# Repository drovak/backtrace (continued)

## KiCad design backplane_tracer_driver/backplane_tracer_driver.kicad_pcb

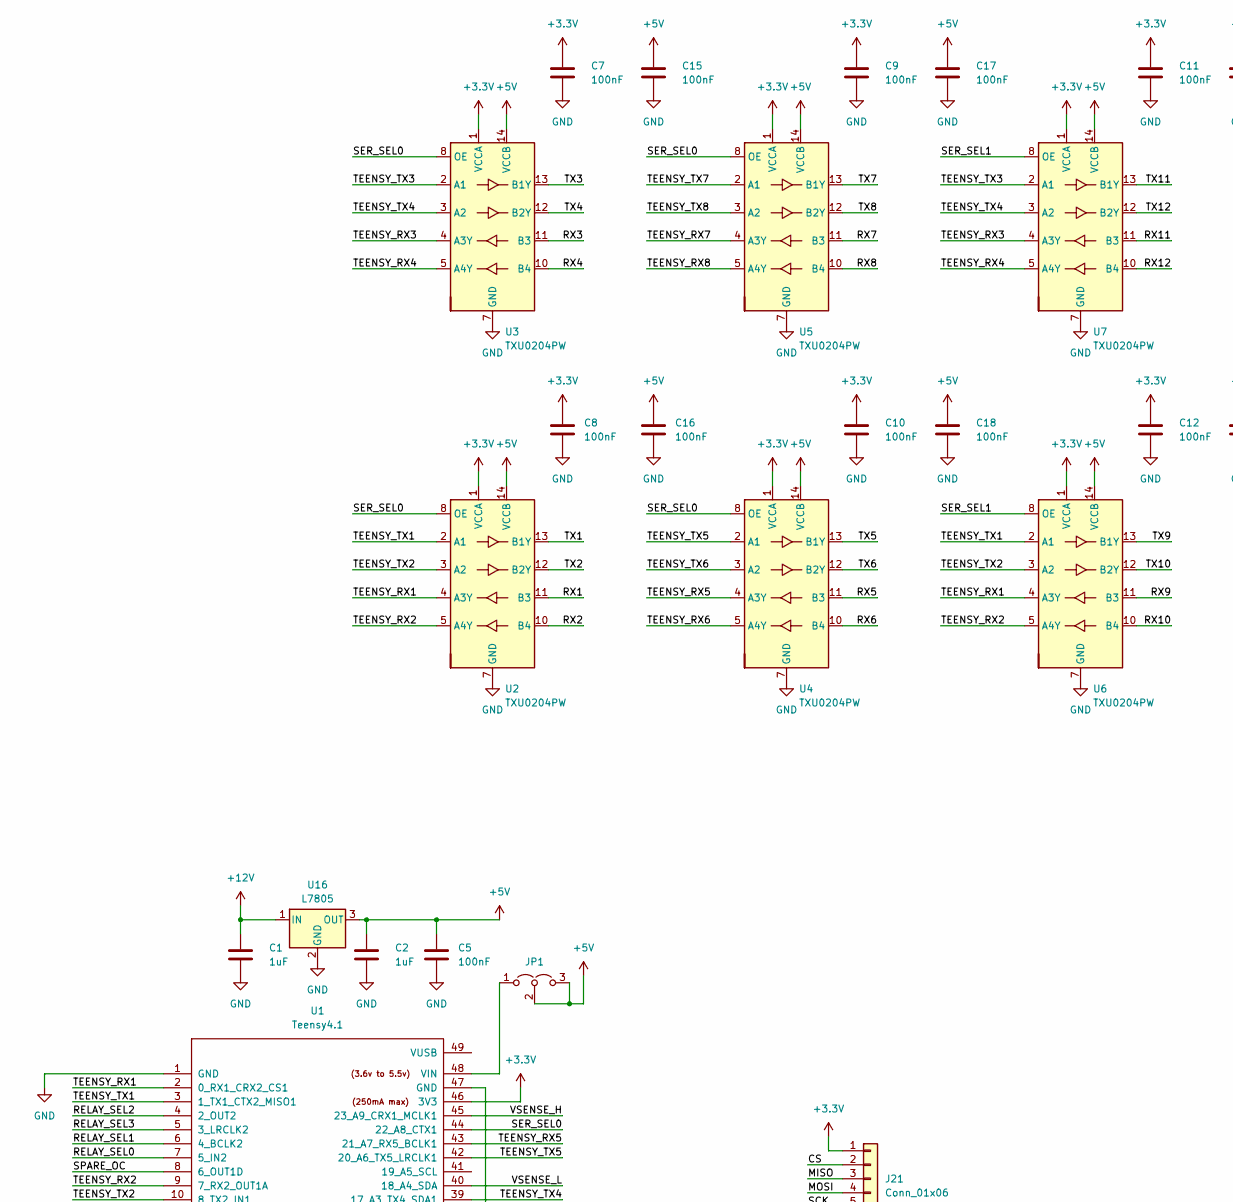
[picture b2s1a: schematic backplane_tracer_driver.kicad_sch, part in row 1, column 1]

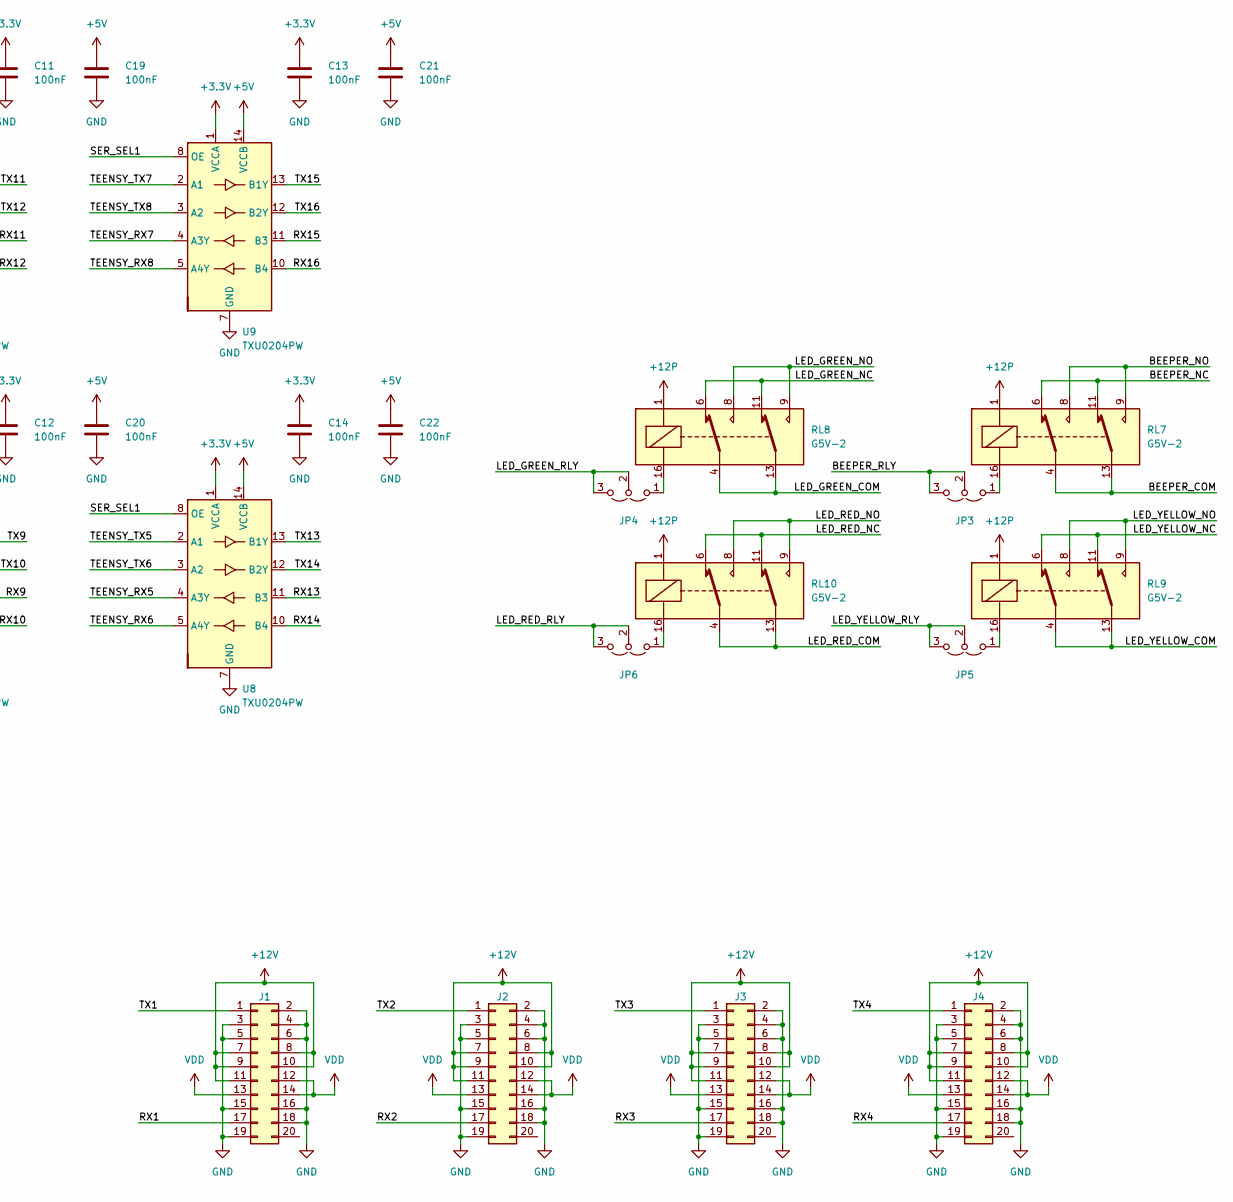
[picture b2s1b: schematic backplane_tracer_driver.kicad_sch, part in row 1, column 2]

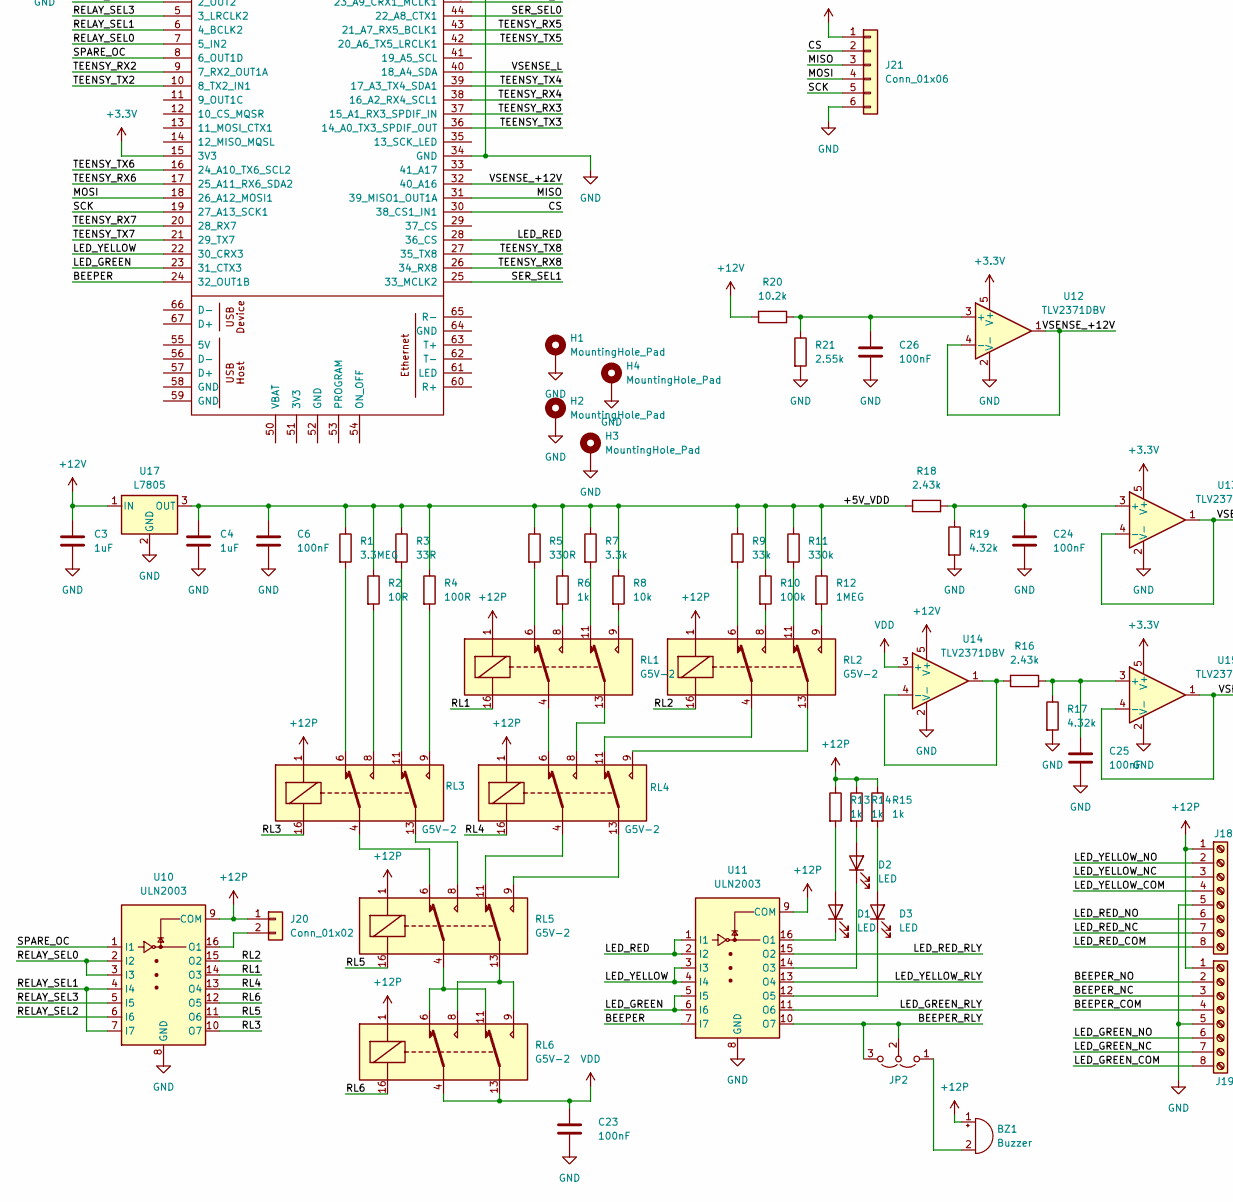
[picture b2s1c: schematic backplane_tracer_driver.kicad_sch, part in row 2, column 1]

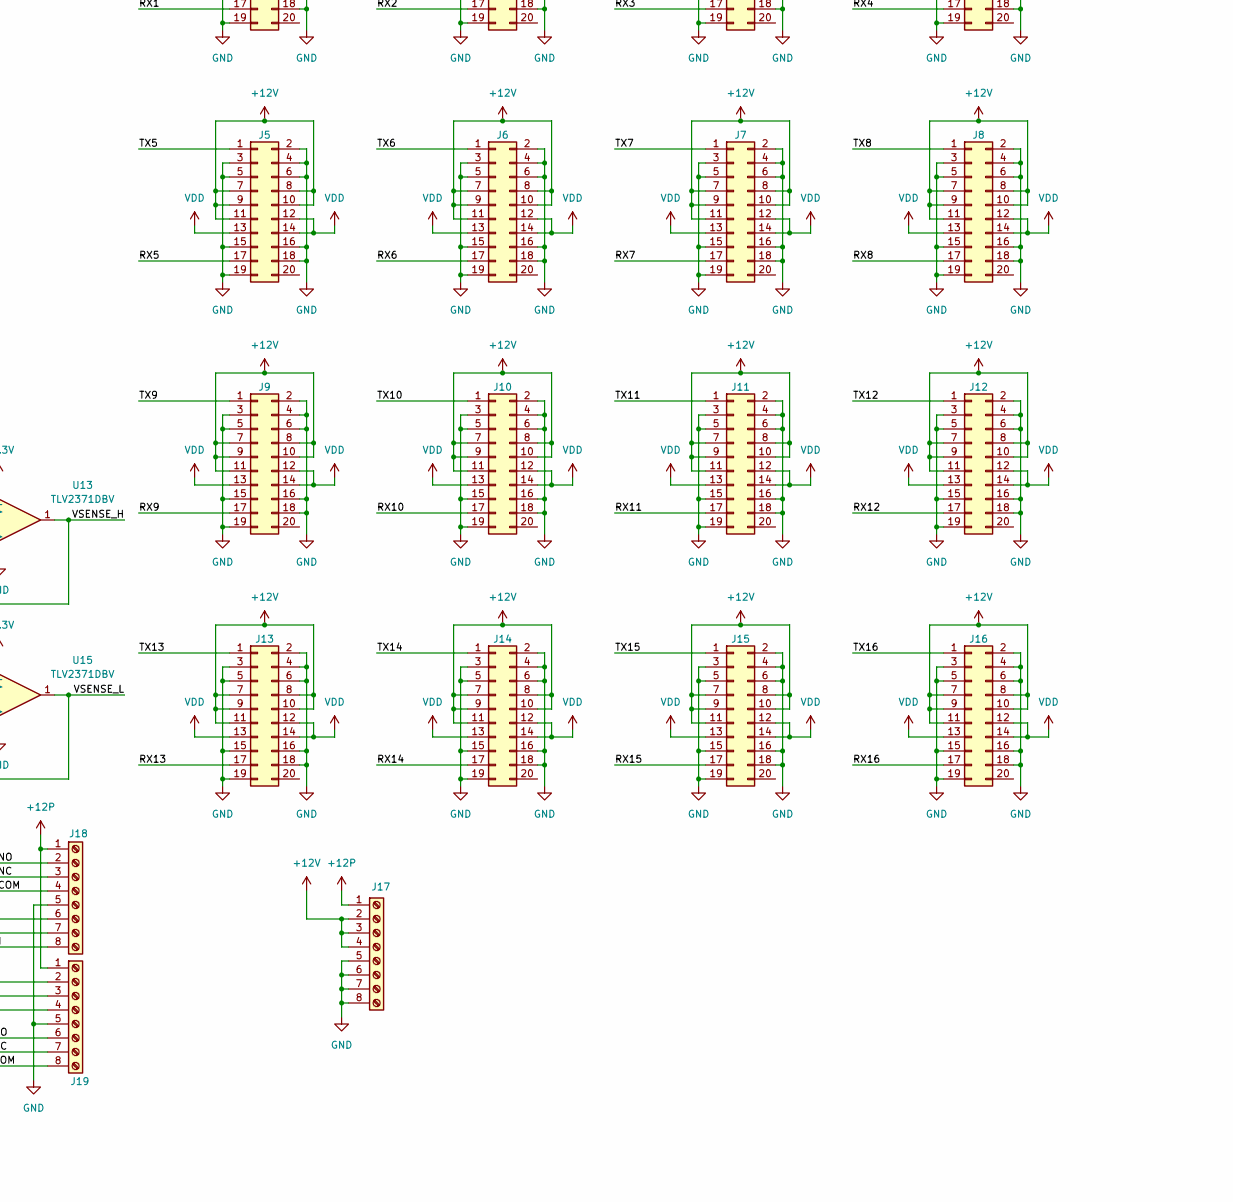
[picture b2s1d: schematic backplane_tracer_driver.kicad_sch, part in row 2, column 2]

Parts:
BZ1: Buzzer; Buzzer_12x9.5RM7.6
C1, C2, C3, C4: 1uF; C_0603_1608Metric_Pad1.08x0.95mm_HandSolder
C5, C6, C7, C8, C9, C10, C11, C12, C13, C14, C15, C16, C17, C18, C19, C20, C21, C22, C23, C24, C25, C26: 100nF; C_0603_1608Metric_Pad1.08x0.95mm_HandSolder
D1, D2, D3: LED; LED_D5.0mm
H1, H2, H3, H4: MountingHole_Pad; MountingHole_3.7mm_Pad_Via
J1, J2, J3, J4, J5, J6, J7, J8, J9, J10, J11, J12, J13, J14, J15, J16: 2x10 right angle IDC connector, 2.54mm pitch; IDC-Header_2x10_P2.54mm_Vertical_alt_silk; LCSC C5372876
J17, J18, J19: Screw_Terminal_01x08; PhoenixContact_PT_1,5_8-5,0-H_1935226
J20: Conn_01x02; PinHeader_1x02_P2.54mm_Vertical
J21: Conn_01x06; PinHeader_1x06_P2.54mm_Vertical
JP1, JP2, JP3, JP4, JP5, JP6: Jumper_3_Open; PinHeader_1x03_P2.54mm_Vertical
R1: 3.3MEG; R_Axial_DIN0207_L6.3mm_D2.5mm_P10.16mm_Horizontal
R2: 10R; R_Axial_Rideon_UB-5C_L0.5in_D0.25in_P0.8in_Horizontal
R3: 33R; R_Axial_DIN0614_L14.3mm_D5.7mm_P20.32mm_Horizontal
R4: 100R; R_Axial_DIN0207_L6.3mm_D2.5mm_P10.16mm_Horizontal
R5: 330R; R_Axial_DIN0204_L3.6mm_D1.6mm_P7.62mm_Horizontal
R6: 1k; R_Axial_DIN0204_L3.6mm_D1.6mm_P7.62mm_Horizontal
R7: 3.3k; R_Axial_DIN0204_L3.6mm_D1.6mm_P7.62mm_Horizontal
R8: 10k; R_Axial_DIN0204_L3.6mm_D1.6mm_P7.62mm_Horizontal
R9: 33k; R_Axial_DIN0204_L3.6mm_D1.6mm_P7.62mm_Horizontal
R10: 100k; R_Axial_DIN0204_L3.6mm_D1.6mm_P7.62mm_Horizontal
R11: 330k; R_Axial_DIN0204_L3.6mm_D1.6mm_P7.62mm_Horizontal
R12: 1MEG; R_Axial_DIN0204_L3.6mm_D1.6mm_P7.62mm_Horizontal
R13, R14, R15: 1k; R_0805_2012Metric
R16, R18: 2.43k; R_0805_2012Metric
R17, R19: 4.32k; R_0805_2012Metric
R20: 10.2k; R_0805_2012Metric
R21: 2.55k; R_0805_2012Metric
RL1, RL2, RL3, RL4, RL5, RL6, RL7, RL8, RL9, RL10: G5V-2; Relay_DPDT_Omron_G5V-2
U1: Teensy4.1; Teensy41
U2, U3, U4, U5, U6, U7, U8, U9: TXU0204PW; TSSOP-14_4.4x5mm_P0.65mm
U10, U11: ULN2003; SOIC-16_3.9x9.9mm_P1.27mm
U12, U13, U14, U15: TLV2371DBV; SOT-23-5
U16, U17: L7805; TO-220-3_Vertical

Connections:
+3.3V: C7.1, C8.1, C9.1, C10.1, C11.1, C12.1, C13.1, C14.1, J21.1, U1.15 (3V3), U1.46 (3V3), U2.1 (VCCA), U3.1 (VCCA), U4.1 (VCCA), U5.1 (VCCA), U6.1 (VCCA), U7.1 (VCCA), U8.1 (VCCA), U9.1 (VCCA), U12.5 (V+), U13.5 (V+), U15.5 (V+)
+5V: C2.1, C5.1, C15.1, C16.1, C17.1, C18.1, C19.1, C20.1, C21.1, C22.1, JP1.2 (C), JP1.3 (B), U2.14 (VCCB), U3.14 (VCCB), U4.14 (VCCB), U5.14 (VCCB), U6.14 (VCCB), U7.14 (VCCB), U8.14 (VCCB), U9.14 (VCCB), U16.3 (OUT)
+12P: BZ1.1 (+), J17.1, J18.1, J19.1, J20.1, R13.1, R14.1, R15.1, RL1.1, RL2.1, RL3.1, RL4.1, RL5.1, RL6.1, RL7.1, RL8.1, RL9.1, RL10.1, U10.9 (COM), U11.9 (COM)
+12V: C1.1, C3.1, J1.7, J1.8, J1.9, J1.10, J1.11, J2.7, J2.8, J2.9, J2.10, J2.11, J3.7, J3.8, J3.9, J3.10, J3.11, J4.7, J4.8, J4.9, J4.10, J4.11, J5.7, J5.8, J5.9, J5.10, J5.11, J6.7, J6.8, J6.9, J6.10, J6.11, J7.7, J7.8, J7.9, J7.10, J7.11, J8.7, J8.8, J8.9, J8.10, J8.11, J9.7, J9.8, J9.9, J9.10, J9.11, J10.7, J10.8, J10.9, J10.10, J10.11, J11.7, J11.8, J11.9, J11.10, J11.11, J12.7, J12.8, J12.9, J12.10, J12.11, J13.7, J13.8, J13.9, J13.10, J13.11, J14.7, J14.8, J14.9, J14.10, J14.11, J15.7, J15.8, J15.9, J15.10, J15.11, J16.7, J16.8, J16.9, J16.10, J16.11, J17.2, J17.3, J17.4, R20.1, U14.5 (V+), U16.1 (IN), U17.1 (IN)
/+5V_VDD: C4.1, C6.1, R1.1, R2.1, R3.1, R4.1, R5.1, R6.1, R7.1, R8.1, R9.1, R10.1, R11.1, R12.1, R18.1, U17.3 (OUT)
/BEEPER: U1.24 (32_OUT1B), U11.7 (I7)
/BEEPER_COM: J19.4, RL7.4, RL7.13
/BEEPER_NC: J19.3, RL7.6, RL7.11
/BEEPER_NO: J19.2, RL7.8, RL7.9
/BEEPER_RLY: JP2.2 (C), JP2.3 (B), JP3.2 (C), JP3.3 (B), U11.10 (O7)
/CS: J21.2, U1.30 (38_CS1_IN1)
/LED_GREEN: U1.23 (31_CTX3), U11.5 (I5), U11.6 (I6)
/LED_GREEN_COM: J19.8, RL8.4, RL8.13
/LED_GREEN_NC: J19.7, RL8.6, RL8.11
/LED_GREEN_NO: J19.6, RL8.8, RL8.9
/LED_GREEN_RLY: JP4.2 (C), JP4.3 (B), U11.11 (O6)
/LED_RED: U1.28 (36_CS), U11.1 (I1), U11.2 (I2)
/LED_RED_COM: J18.8, RL10.4, RL10.13
/LED_RED_NC: J18.7, RL10.6, RL10.11
/LED_RED_NO: J18.6, RL10.8, RL10.9
/LED_RED_RLY: JP6.2 (C), JP6.3 (B), U11.15 (O2)
/LED_YELLOW: U1.22 (30_CRX3), U11.3 (I3), U11.4 (I4)
/LED_YELLOW_COM: J18.4, RL9.4, RL9.13
/LED_YELLOW_NC: J18.3, RL9.6, RL9.11
/LED_YELLOW_NO: J18.2, RL9.8, RL9.9
/LED_YELLOW_RLY: JP5.2 (C), JP5.3 (B), U11.13 (O4)
/MISO: J21.3, U1.31 (39_MISO1_OUT1A)
/MOSI: J21.4, U1.18 (26_A12_MOSI1)
/RELAY_SEL0: U1.7 (5_IN2), U10.2 (I2), U10.3 (I3)
/RELAY_SEL1: U1.6 (4_BCLK2), U10.4 (I4), U10.7 (I7)
/RELAY_SEL2: U1.4 (2_OUT2), U10.6 (I6)
/RELAY_SEL3: U1.5 (3_LRCLK2), U10.5 (I5)
/RL1: RL1.16, U10.14 (O3)
/RL2: RL2.16, U10.15 (O2)
/RL3: RL3.16, U10.10 (O7)
/RL4: RL4.16, U10.13 (O4)
/RL5: RL5.16, U10.11 (O6)
/RL6: RL6.16, U10.12 (O5)
/RX1: J1.17, U2.11 (B3)
/RX2: J2.17, U2.10 (B4)
/RX3: J3.17, U3.11 (B3)
/RX4: J4.17, U3.10 (B4)
/RX5: J5.17, U4.11 (B3)
/RX6: J6.17, U4.10 (B4)
/RX7: J7.17, U5.11 (B3)
/RX8: J8.17, U5.10 (B4)
/RX9: J9.17, U6.11 (B3)
/RX10: J10.17, U6.10 (B4)
/RX11: J11.17, U7.11 (B3)
/RX12: J12.17, U7.10 (B4)
/RX13: J13.17, U8.11 (B3)
/RX14: J14.17, U8.10 (B4)
/RX15: J15.17, U9.11 (B3)
/RX16: J16.17, U9.10 (B4)
/SCK: J21.5, U1.19 (27_A13_SCK1)
/SER_SEL0: U1.44 (22_A8_CTX1), U2.8 (OE), U3.8 (OE), U4.8 (OE), U5.8 (OE)
/SER_SEL1: U1.25 (33_MCLK2), U6.8 (OE), U7.8 (OE), U8.8 (OE), U9.8 (OE)
/SPARE_OC: U1.8 (6_OUT1D), U10.1 (I1)
/TEENSY_RX1: U1.2 (0_RX1_CRX2_CS1), U2.4 (A3Y), U6.4 (A3Y)
/TEENSY_RX2: U1.9 (7_RX2_OUT1A), U2.5 (A4Y), U6.5 (A4Y)
/TEENSY_RX3: U1.37 (15_A1_RX3_SPDIF_IN), U3.4 (A3Y), U7.4 (A3Y)
/TEENSY_RX4: U1.38 (16_A2_RX4_SCL1), U3.5 (A4Y), U7.5 (A4Y)
/TEENSY_RX5: U1.43 (21_A7_RX5_BCLK1), U4.4 (A3Y), U8.4 (A3Y)
/TEENSY_RX6: U1.17 (25_A11_RX6_SDA2), U4.5 (A4Y), U8.5 (A4Y)
/TEENSY_RX7: U1.20 (28_RX7), U5.4 (A3Y), U9.4 (A3Y)
/TEENSY_RX8: U1.26 (34_RX8), U5.5 (A4Y), U9.5 (A4Y)
/TEENSY_TX1: U1.3 (1_TX1_CTX2_MISO1), U2.2 (A1), U6.2 (A1)
/TEENSY_TX2: U1.10 (8_TX2_IN1), U2.3 (A2), U6.3 (A2)
/TEENSY_TX3: U1.36 (14_A0_TX3_SPDIF_OUT), U3.2 (A1), U7.2 (A1)
/TEENSY_TX4: U1.39 (17_A3_TX4_SDA1), U3.3 (A2), U7.3 (A2)
/TEENSY_TX5: U1.42 (20_A6_TX5_LRCLK1), U4.2 (A1), U8.2 (A1)
/TEENSY_TX6: U1.16 (24_A10_TX6_SCL2), U4.3 (A2), U8.3 (A2)
/TEENSY_TX7: U1.21 (29_TX7), U5.2 (A1), U9.2 (A1)
/TEENSY_TX8: U1.27 (35_TX8), U5.3 (A2), U9.3 (A2)
/TX1: J1.1, U2.13 (B1Y)
/TX2: J2.1, U2.12 (B2Y)
/TX3: J3.1, U3.13 (B1Y)
/TX4: J4.1, U3.12 (B2Y)
/TX5: J5.1, U4.13 (B1Y)
/TX6: J6.1, U4.12 (B2Y)
/TX7: J7.1, U5.13 (B1Y)
/TX8: J8.1, U5.12 (B2Y)
/TX9: J9.1, U6.13 (B1Y)
/TX10: J10.1, U6.12 (B2Y)
/TX11: J11.1, U7.13 (B1Y)
/TX12: J12.1, U7.12 (B2Y)
/TX13: J13.1, U8.13 (B1Y)
/TX14: J14.1, U8.12 (B2Y)
/TX15: J15.1, U9.13 (B1Y)
/TX16: J16.1, U9.12 (B2Y)
/VSENSE_+12V: U1.32 (40_A16), U12.1, U12.4 (-)
/VSENSE_H: U1.45 (23_A9_CRX1_MCLK1), U13.1, U13.4 (-)
/VSENSE_L: U1.40 (18_A4_SDA), U15.1, U15.4 (-)
GND: C1.2, C2.2, C3.2, C4.2, C5.2, C6.2, C7.2, C8.2, C9.2, C10.2, C11.2, C12.2, C13.2, C14.2, C15.2, C16.2, C17.2, C18.2, C19.2, C20.2, C21.2, C22.2, C23.2, C24.2, C25.2, C26.2, H1.1, H2.1, H3.1, H4.1, J1.2, J1.3, J1.4, J1.5, J1.6, J1.15, J1.16, J1.18, J1.19, J2.2, J2.3, J2.4, J2.5, J2.6, J2.15, J2.16, J2.18, J2.19, J3.2, J3.3, J3.4, J3.5, J3.6, J3.15, J3.16, J3.18, J3.19, J4.2, J4.3, J4.4, J4.5, J4.6, J4.15, J4.16, J4.18, J4.19, J5.2, J5.3, J5.4, J5.5, J5.6, J5.15, J5.16, J5.18, J5.19, J6.2, J6.3, J6.4, J6.5, J6.6, J6.15, J6.16, J6.18, J6.19, J7.2, J7.3, J7.4, J7.5, J7.6, J7.15, J7.16, J7.18, J7.19, J8.2, J8.3, J8.4, J8.5, J8.6, J8.15, J8.16, J8.18, J8.19, J9.2, J9.3, J9.4, J9.5, J9.6, J9.15, J9.16, J9.18, J9.19, J10.2, J10.3, J10.4, J10.5, J10.6, J10.15, J10.16, J10.18, J10.19, J11.2, J11.3, J11.4, J11.5, J11.6, J11.15, J11.16, J11.18, J11.19, J12.2, J12.3, J12.4, J12.5, J12.6, J12.15, J12.16, J12.18, J12.19, J13.2, J13.3, J13.4, J13.5, J13.6, J13.15, J13.16, J13.18, J13.19, J14.2, J14.3, J14.4, J14.5, J14.6, J14.15, J14.16, J14.18, J14.19, J15.2, J15.3, J15.4, J15.5, J15.6, J15.15, J15.16, J15.18, J15.19, J16.2, J16.3, J16.4, J16.5, J16.6, J16.15, J16.16, J16.18, J16.19, J17.5, J17.6, J17.7, J17.8, J18.5, J19.5, J21.6, R17.2, R19.2, R21.2, U1.1 (GND), U1.34 (GND), U1.47 (GND), U2.7 (GND), U3.7 (GND), U4.7 (GND), U5.7 (GND), U6.7 (GND), U7.7 (GND), U8.7 (GND), U9.7 (GND), U10.8 (GND), U11.8 (GND), U12.2 (V-), U13.2 (V-), U14.2 (V-), U15.2 (V-), U16.2 (GND), U17.2 (GND)
unnamed: BZ1.2 (-), JP2.1 (A)
unnamed: D1.2 (A), R13.2
unnamed: D1.1 (K), U11.16 (O1)
unnamed: D2.2 (A), R14.2
unnamed: D2.1 (K), U11.14 (O3)
unnamed: D3.2 (A), R15.2
unnamed: D3.1 (K), U11.12 (O5)
unnamed: J20.2, U10.16 (O1)
unnamed: JP1.1 (A), U1.48 (VIN)
unnamed: JP3.1 (A), RL7.16
unnamed: JP4.1 (A), RL8.16
unnamed: JP5.1 (A), RL9.16
unnamed: JP6.1 (A), RL10.16
unnamed: R1.2, RL3.6
unnamed: R2.2, RL3.8
unnamed: R3.2, RL3.11
unnamed: R4.2, RL3.9
unnamed: R5.2, RL1.6
unnamed: R6.2, RL1.8
unnamed: R7.2, RL1.11
unnamed: R8.2, RL1.9
unnamed: R9.2, RL2.6
unnamed: R10.2, RL2.8
unnamed: R11.2, RL2.11
unnamed: R12.2, RL2.9
unnamed: RL1.4, RL4.6
unnamed: RL1.13, RL4.8
unnamed: RL2.4, RL4.11
unnamed: RL2.13, RL4.9
unnamed: RL3.4, RL5.6
unnamed: RL3.13, RL5.8
unnamed: RL4.4, RL5.11
unnamed: RL4.13, RL5.9
unnamed: RL5.4, RL6.6, RL6.11
unnamed: RL5.13, RL6.8, RL6.9
unnamed: C26.1, R20.2, R21.1, U12.3 (+)
unnamed: C24.1, R18.2, R19.1, U13.3 (+)
unnamed: R16.1, U14.1, U14.4 (-)
unnamed: C25.1, R16.2, R17.1, U15.3 (+)
VDD: C23.1, J1.12, J1.13, J1.14, J2.12, J2.13, J2.14, J3.12, J3.13, J3.14, J4.12, J4.13, J4.14, J5.12, J5.13, J5.14, J6.12, J6.13, J6.14, J7.12, J7.13, J7.14, J8.12, J8.13, J8.14, J9.12, J9.13, J9.14, J10.12, J10.13, J10.14, J11.12, J11.13, J11.14, J12.12, J12.13, J12.14, J13.12, J13.13, J13.14, J14.12, J14.13, J14.14, J15.12, J15.13, J15.14, J16.12, J16.13, J16.14, RL6.4, RL6.13, U14.3 (+)

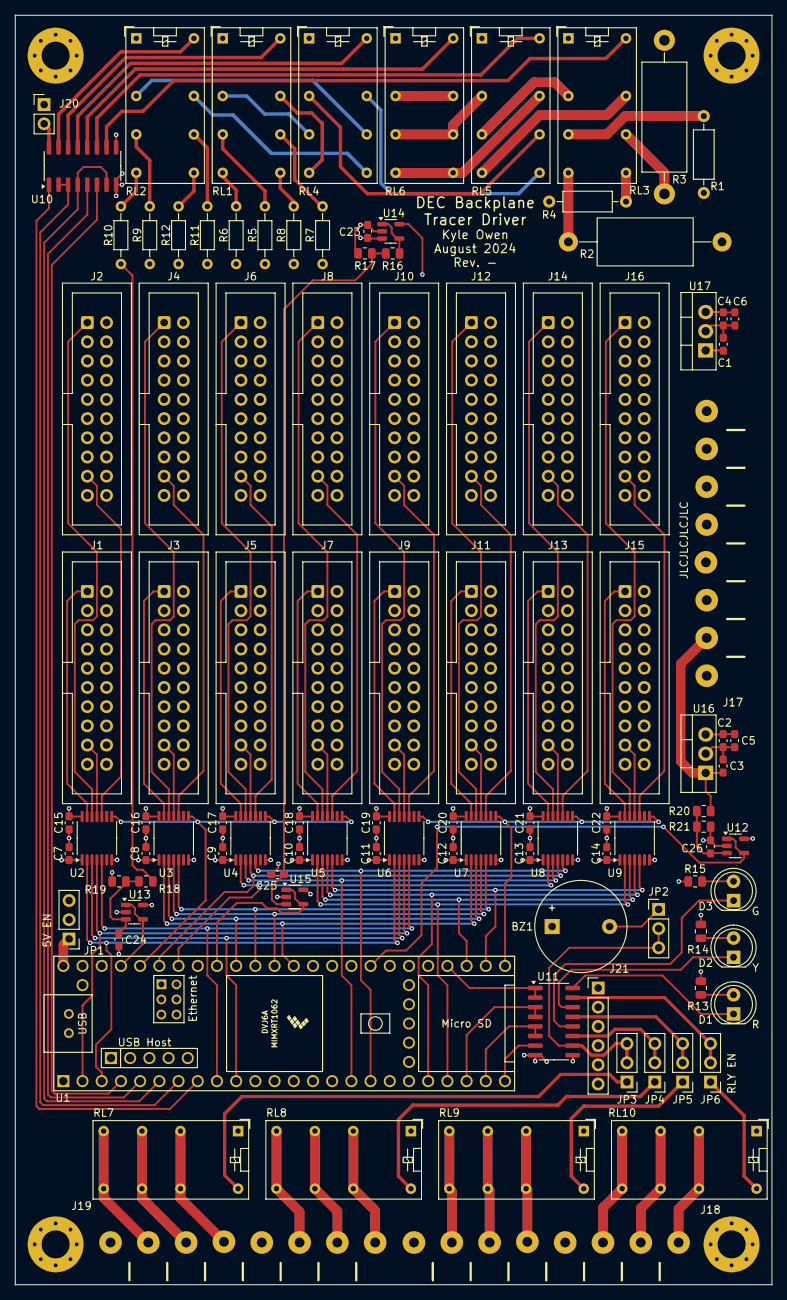
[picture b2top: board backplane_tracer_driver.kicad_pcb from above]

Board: 4 copper layers, 100.1 x 167.9 mm, 109 parts (0 on the bottom side), 134 nets.

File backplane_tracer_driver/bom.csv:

"Reference","Value","Footprint","Qty"
"BZ1","Buzzer","Buzzer_Beeper:Buzzer_12x9.5RM7.6","1"
"C1,C2,C3,C4","1uF","Capacitor_SMD:C_0603_1608Metric_Pad1.08x0.95mm_HandSolder","4"
"C5,C6,C7,C8,C9,C10,C11,C12,C13,C14,C15,C16,C17,C18,C19,C20,C21,C22,C23,C24,C25,C26","100nF","Capacitor_SMD:C_0603_1608Metric_Pad1.08x0.95mm_HandSolder","22"
"D1,D2,D3","LED","LED_THT:LED_D5.0mm","3"
"J1,J2,J3,J4,J5,J6,J7,J8,J9,J10,J11,J12,J13,J14,J15,J16","2x10 right angle IDC connector, 2.54mm pitch","Connector_IDC:IDC-Header_2x10_P2.54mm_Vertical_alt_silk","16"
"J17,J18,J19","Screw_Terminal_01x08","Connector_Phoenix_PT:PhoenixContact_PT_1,5_8-5,0-H_1935226","3"
"R1","3.3MEG","Resistor_THT:R_Axial_DIN0207_L6.3mm_D2.5mm_P10.16mm_Horizontal","1"
"R2","10R","Resistor_THT:R_Axial_Rideon_UB-5C_L0.5in_D0.25in_P0.8in_Horizontal","1"
"R3","33R","Resistor_THT:R_Axial_DIN0614_L14.3mm_D5.7mm_P20.32mm_Horizontal","1"
"R4","100R","Resistor_THT:R_Axial_DIN0207_L6.3mm_D2.5mm_P10.16mm_Horizontal","1"
"R5","330R","Resistor_THT:R_Axial_DIN0204_L3.6mm_D1.6mm_P7.62mm_Horizontal","1"
"R6,R13,R14,R15","1k","-- mixed values --","4"
"R7","3.3k","Resistor_THT:R_Axial_DIN0204_L3.6mm_D1.6mm_P7.62mm_Horizontal","1"
"R8","10k","Resistor_THT:R_Axial_DIN0204_L3.6mm_D1.6mm_P7.62mm_Horizontal","1"
"R9","33k","Resistor_THT:R_Axial_DIN0204_L3.6mm_D1.6mm_P7.62mm_Horizontal","1"
"R10","100k","Resistor_THT:R_Axial_DIN0204_L3.6mm_D1.6mm_P7.62mm_Horizontal","1"
"R11","330k","Resistor_THT:R_Axial_DIN0204_L3.6mm_D1.6mm_P7.62mm_Horizontal","1"
"R12","1MEG","Resistor_THT:R_Axial_DIN0204_L3.6mm_D1.6mm_P7.62mm_Horizontal","1"
"R16,R18","2.43k","Resistor_SMD:R_0805_2012Metric","2"
"R17,R19","4.32k","Resistor_SMD:R_0805_2012Metric","2"
"R20","10.2k","Resistor_SMD:R_0805_2012Metric","1"
"R21","2.55k","Resistor_SMD:R_0805_2012Metric","1"
"RL1,RL2,RL3,RL4,RL5,RL6,RL7,RL8,RL9,RL10","JW2","Relay_THT:Relay_DPDT_Panasonic_JW2","10"
"U1","Teensy4.1","teensy:Teensy41","1"
"U2,U3,U4,U5,U6,U7,U8,U9","TXU0204PW","Package_SO:TSSOP-14_4.4x5mm_P0.65mm","8"
"U10,U11","ULN2003","Package_SO:SOIC-16_3.9x9.9mm_P1.27mm","2"
"U12,U13,U14,U15","TLV2371DBV","Package_TO_SOT_SMD:SOT-23-5","4"
"U16,U17","L7805","Package_TO_SOT_THT:TO-220-3_Vertical","2"

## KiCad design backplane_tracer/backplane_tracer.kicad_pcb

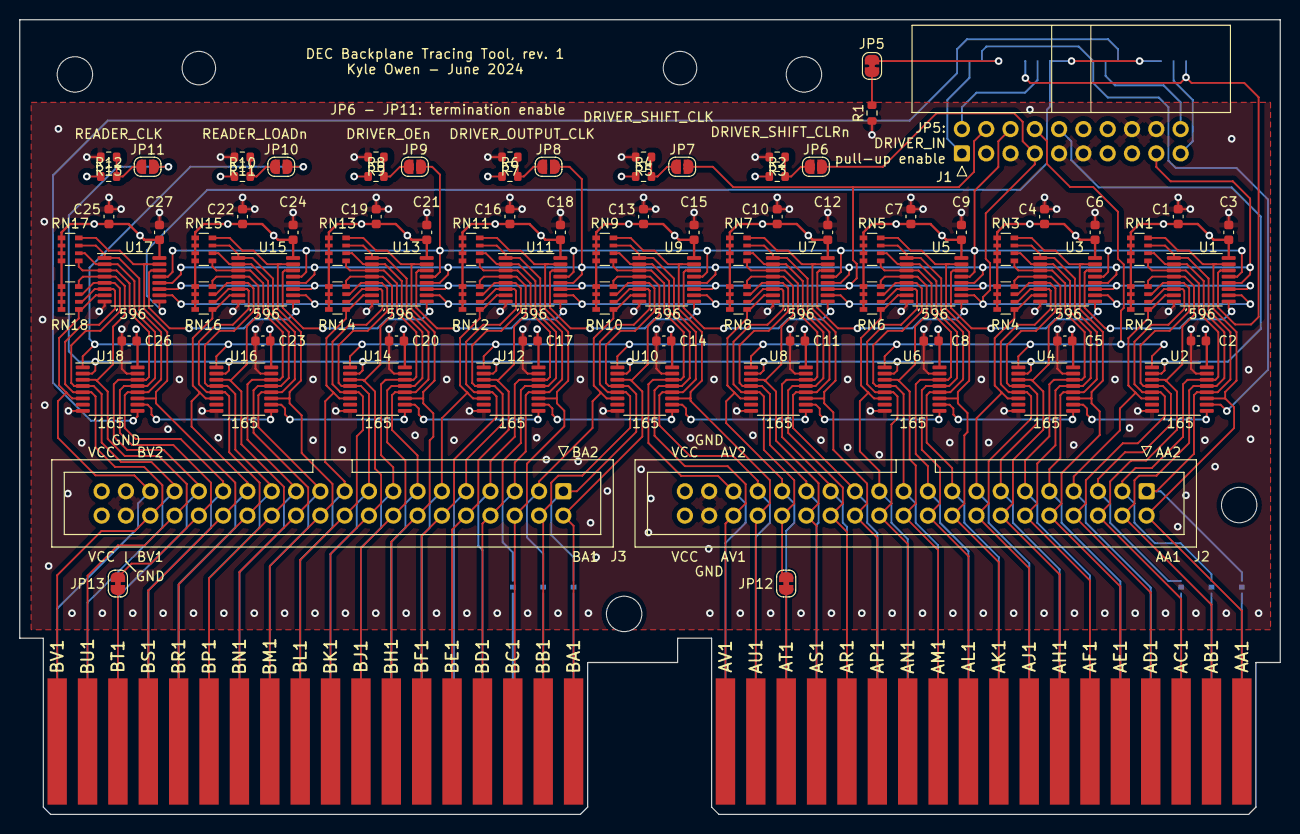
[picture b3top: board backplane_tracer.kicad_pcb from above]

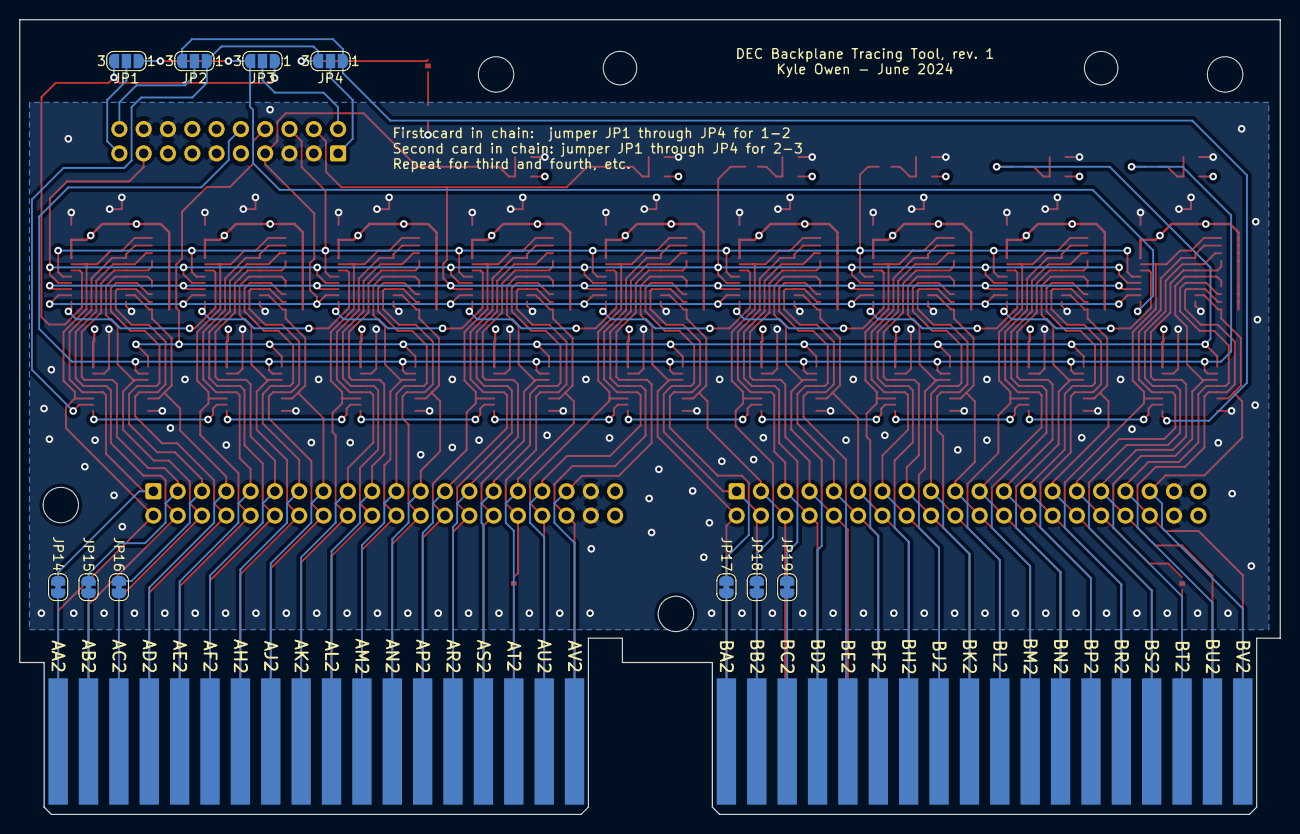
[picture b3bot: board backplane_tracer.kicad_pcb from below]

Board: 4 copper layers, 131.7 x 83.1 mm, 105 parts (10 on the bottom side), 119 nets.

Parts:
C1, C4, C7, C10, C13, C16, C19, C22, C25: 1uF; C_0603_1608Metric
C2, C3, C5, C6, C8, C9, C11, C12, C14, C15, C17, C18, C20, C21, C23, C24, C26, C27: 0.1uF; C_0603_1608Metric
H1, H2: MountingHole; MountingHole_3.5mm
H3, H4, H5, H6: MountingHole; MountingHole_3.7mm
J1: Conn_02x10_Odd_Even; IDC-Header_2x10_P2.54mm_Horizontal
J2, J3: Conn_02x20_Odd_Even; IDC-Header_2x20_P2.54mm_Vertical
J4: CONN-DEC-DOUBLE
JP1, JP2, JP3, JP4: SolderJumper_3_Open; SolderJumper-3_P1.3mm_Open_RoundedPad1.0x1.5mm_NumberLabels
JP5: SolderJumper_2_Bridged; SolderJumper-2_P1.3mm_Bridged_RoundedPad1.0x1.5mm
JP6, JP7, JP8, JP9, JP10, JP11: SolderJumper_2_Open; SolderJumper-2_P1.3mm_Open_RoundedPad1.0x1.5mm
JP12, JP13, JP14, JP15, JP16, JP17, JP18, JP19: Jumper_2_Bridged; SolderJumper-2_P1.3mm_Bridged_RoundedPad1.0x1.5mm
R1: 10k; R_0603_1608Metric
R2, R3, R4, R5, R6, R7, R8, R9, R10, R11, R12, R13: R; R_0603_1608Metric
RN1, RN2, RN3, RN4, RN5, RN6, RN7, RN8, RN9, RN10, RN11, RN12, RN13, RN14, RN15, RN16, RN17, RN18: 470k; R_Array_Convex_4x0603
U1, U3, U5, U7, U9, U11, U13, U15, U17: 74HCS596; TSSOP-16_4.4x5mm_P0.65mm
U2, U4, U6, U8, U10, U12, U14, U16, U18: 74HCS165; TSSOP-16_4.4x5mm_P0.65mm

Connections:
+5V: C1.1, C2.1, C3.1, C4.1, C5.1, C6.1, C7.1, C8.1, C9.1, C10.1, C11.1, C12.1, C13.1, C14.1, C15.1, C16.1, C17.1, C18.1, C19.1, C20.1, C21.1, C22.1, C23.1, C24.1, C25.1, C26.1, C27.1, J1.12, J1.13, J1.14, J1.15, J2.39, J2.40, J3.39, J3.40, R2.1, R4.1, R6.1, R8.1, R10.1, R12.1, RN1.1 (R1.1), RN1.2 (R2.1), RN1.3 (R3.1), RN1.4 (R4.1), RN2.1 (R1.1), RN2.2 (R2.1), RN2.3 (R3.1), RN2.4 (R4.1), RN3.1 (R1.1), RN3.2 (R2.1), RN3.3 (R3.1), RN3.4 (R4.1), RN4.1 (R1.1), RN4.2 (R2.1), RN4.3 (R3.1), RN4.4 (R4.1), RN5.1 (R1.1), RN5.2 (R2.1), RN5.3 (R3.1), RN5.4 (R4.1), RN6.1 (R1.1), RN6.2 (R2.1), RN6.3 (R3.1), RN6.4 (R4.1), RN7.1 (R1.1), RN7.2 (R2.1), RN7.3 (R3.1), RN7.4 (R4.1), RN8.1 (R1.1), RN8.2 (R2.1), RN8.3 (R3.1), RN8.4 (R4.1), RN9.1 (R1.1), RN9.2 (R2.1), RN9.3 (R3.1), RN9.4 (R4.1), RN10.1 (R1.1), RN10.2 (R2.1), RN10.3 (R3.1), RN10.4 (R4.1), RN11.1 (R1.1), RN11.2 (R2.1), RN11.3 (R3.1), RN11.4 (R4.1), RN12.1 (R1.1), RN12.2 (R2.1), RN12.3 (R3.1), RN12.4 (R4.1), RN13.1 (R1.1), RN13.2 (R2.1), RN13.3 (R3.1), RN13.4 (R4.1), RN14.1 (R1.1), RN14.2 (R2.1), RN14.3 (R3.1), RN14.4 (R4.1), RN15.1 (R1.1), RN15.2 (R2.1), RN15.3 (R3.1), RN15.4 (R4.1), RN16.1 (R1.1), RN16.2 (R2.1), RN16.3 (R3.1), RN16.4 (R4.1), RN17.1 (R1.1), RN17.2 (R2.1), RN17.3 (R3.1), RN17.4 (R4.1), RN18.1 (R1.1), RN18.2 (R2.1), RN18.3 (R3.1), RN18.4 (R4.1), U1.16 (VCC), U2.16 (VCC), U3.16 (VCC), U4.16 (VCC), U5.16 (VCC), U6.16 (VCC), U7.16 (VCC), U8.16 (VCC), U9.16 (VCC), U10.16 (VCC), U11.16 (VCC), U12.16 (VCC), U13.16 (VCC), U14.16 (VCC), U15.16 (VCC), U16.16 (VCC), U17.16 (VCC), U18.16 (VCC)
/8bit_element0/DRIVER_OUT: U1.9 (QH'), U3.14 (SER)
/8bit_element0/READER_OUT: U2.9 (Q7), U4.10 (DS)
/8bit_element1/DRIVER_OUT: U3.9 (QH'), U5.14 (SER)
/8bit_element1/READER_OUT: U4.9 (Q7), U6.10 (DS)
/8bit_element2/DRIVER_OUT: U5.9 (QH'), U7.14 (SER)
/8bit_element2/READER_OUT: U6.9 (Q7), U8.10 (DS)
/8bit_element3/DRIVER_OUT: U7.9 (QH'), U9.14 (SER)
/8bit_element3/READER_OUT: U8.9 (Q7), U10.10 (DS)
/8bit_element4/DRIVER_OUT: U9.9 (QH'), U11.14 (SER)
/8bit_element4/READER_OUT: U10.9 (Q7), U12.10 (DS)
/8bit_element5/DRIVER_OUT: U11.9 (QH'), U13.14 (SER)
/8bit_element5/READER_OUT: U12.9 (Q7), U14.10 (DS)
/8bit_element6/DRIVER_OUT: U13.9 (QH'), U15.14 (SER)
/8bit_element6/READER_OUT: U14.9 (Q7), U16.10 (DS)
/8bit_element7/DRIVER_OUT: U15.9 (QH'), U17.14 (SER)
/8bit_element7/READER_OUT: U16.9 (Q7), U18.10 (DS)
/AA1: J2.2, J4.AA1, RN1.8 (R1.2), U1.15 (QA), U2.11 (D0)
/AA2: J2.1, JP14.2 (B), RN1.7 (R2.2), U1.1 (QB), U2.12 (D1)
/AB1: J2.4, J4.AB1, RN1.6 (R3.2), U1.2 (QC), U2.13 (D2)
/AB2: J2.3, JP15.2 (B), RN1.5 (R4.2), U1.3 (QD), U2.14 (D3)
/AC1: J2.6, J4.AC1, RN2.8 (R1.2), U1.4 (QE), U2.3 (D4)
/AC2: J2.5, JP16.2 (B), RN2.7 (R2.2), U1.5 (QF), U2.4 (D5)
/AD1: J2.8, J4.AD1, RN2.6 (R3.2), U1.6 (QG), U2.5 (D6)
/AD2: J2.7, J4.AD2, RN2.5 (R4.2), U1.7 (QH), U2.6 (D7)
/AE1: J2.10, J4.AE1, RN3.8 (R1.2), U3.15 (QA), U4.11 (D0)
/AE2: J2.9, J4.AE2, RN3.7 (R2.2), U3.1 (QB), U4.12 (D1)
/AF1: J2.12, J4.AF1, RN3.6 (R3.2), U3.2 (QC), U4.13 (D2)
/AF2: J2.11, J4.AF2, RN3.5 (R4.2), U3.3 (QD), U4.14 (D3)
/AH1: J2.14, J4.AH1, RN4.8 (R1.2), U3.4 (QE), U4.3 (D4)
/AH2: J2.13, J4.AH2, RN4.7 (R2.2), U3.5 (QF), U4.4 (D5)
/AJ1: J2.16, J4.AJ1, RN4.6 (R3.2), U3.6 (QG), U4.5 (D6)
/AJ2: J2.15, J4.AJ2, RN4.5 (R4.2), U3.7 (QH), U4.6 (D7)
/AK1: J2.18, J4.AK1, RN5.8 (R1.2), U5.15 (QA), U6.11 (D0)
/AK2: J2.17, J4.AK2, RN5.7 (R2.2), U5.1 (QB), U6.12 (D1)
/AL1: J2.20, J4.AL1, RN5.6 (R3.2), U5.2 (QC), U6.13 (D2)
/AL2: J2.19, J4.AL2, RN5.5 (R4.2), U5.3 (QD), U6.14 (D3)
/AM1: J2.22, J4.AM1, RN6.8 (R1.2), U5.4 (QE), U6.3 (D4)
/AM2: J2.21, J4.AM2, RN6.7 (R2.2), U5.5 (QF), U6.4 (D5)
/AN1: J2.24, J4.AN1, RN6.6 (R3.2), U5.6 (QG), U6.5 (D6)
/AN2: J2.23, J4.AN2, RN6.5 (R4.2), U5.7 (QH), U6.6 (D7)
/AP1: J2.26, J4.AP1, RN7.8 (R1.2), U7.15 (QA), U8.11 (D0)
/AP2: J2.25, J4.AP2, RN7.7 (R2.2), U7.1 (QB), U8.12 (D1)
/AR1: J2.28, J4.AR1, RN7.6 (R3.2), U7.2 (QC), U8.13 (D2)
/AR2: J2.27, J4.AR2, RN7.5 (R4.2), U7.3 (QD), U8.14 (D3)
/AS1: J2.30, J4.AS1, RN8.8 (R1.2), U7.4 (QE), U8.3 (D4)
/AS2: J2.29, J4.AS2, RN8.7 (R2.2), U7.5 (QF), U8.4 (D5)
/AT1: J2.32, JP12.2 (B), RN8.6 (R3.2), U7.6 (QG), U8.5 (D6)
/AT2: J2.31, J4.AT2, RN8.5 (R4.2), U7.7 (QH), U8.6 (D7)
/AU1: J2.34, J4.AU1, RN9.8 (R1.2), U9.15 (QA), U10.11 (D0)
/AU2: J2.33, J4.AU2, RN9.7 (R2.2), U9.1 (QB), U10.12 (D1)
/AV1: J2.36, J4.AV1, RN9.6 (R3.2), U9.2 (QC), U10.13 (D2)
/AV2: J2.35, J4.AV2, RN9.5 (R4.2), U9.3 (QD), U10.14 (D3)
/BA1: J3.2, J4.BA1, RN10.8 (R1.2), U9.4 (QE), U10.3 (D4)
/BA2: J3.1, JP17.2 (B), RN10.7 (R2.2), U9.5 (QF), U10.4 (D5)
/BB1: J3.4, J4.BB1, RN10.6 (R3.2), U9.6 (QG), U10.5 (D6)
/BB2: J3.3, JP18.2 (B), RN10.5 (R4.2), U9.7 (QH), U10.6 (D7)
/BC1: J3.6, J4.BC1, RN11.8 (R1.2), U11.15 (QA), U12.11 (D0)
/BC2: J3.5, JP19.2 (B), RN11.7 (R2.2), U11.1 (QB), U12.12 (D1)
/BD1: J3.8, J4.BD1, RN11.6 (R3.2), U11.2 (QC), U12.13 (D2)
/BD2: J3.7, J4.BD2, RN11.5 (R4.2), U11.3 (QD), U12.14 (D3)
/BE1: J3.10, J4.BE1, RN12.8 (R1.2), U11.4 (QE), U12.3 (D4)
/BE2: J3.9, J4.BE2, RN12.7 (R2.2), U11.5 (QF), U12.4 (D5)
/BF1: J3.12, J4.BF1, RN12.6 (R3.2), U11.6 (QG), U12.5 (D6)
/BF2: J3.11, J4.BF2, RN12.5 (R4.2), U11.7 (QH), U12.6 (D7)
/BH1: J3.14, J4.BH1, RN13.8 (R1.2), U13.15 (QA), U14.11 (D0)
/BH2: J3.13, J4.BH2, RN13.7 (R2.2), U13.1 (QB), U14.12 (D1)
/BJ1: J3.16, J4.BJ1, RN13.6 (R3.2), U13.2 (QC), U14.13 (D2)
/BJ2: J3.15, J4.BJ2, RN13.5 (R4.2), U13.3 (QD), U14.14 (D3)
/BK1: J3.18, J4.BK1, RN14.8 (R1.2), U13.4 (QE), U14.3 (D4)
/BK2: J3.17, J4.BK2, RN14.7 (R2.2), U13.5 (QF), U14.4 (D5)
/BL1: J3.20, J4.BL1, RN14.6 (R3.2), U13.6 (QG), U14.5 (D6)
/BL2: J3.19, J4.BL2, RN14.5 (R4.2), U13.7 (QH), U14.6 (D7)
/BM1: J3.22, J4.BM1, RN15.8 (R1.2), U15.15 (QA), U16.11 (D0)
/BM2: J3.21, J4.BM2, RN15.7 (R2.2), U15.1 (QB), U16.12 (D1)
/BN1: J3.24, J4.BN1, RN15.6 (R3.2), U15.2 (QC), U16.13 (D2)
/BN2: J3.23, J4.BN2, RN15.5 (R4.2), U15.3 (QD), U16.14 (D3)
/BP1: J3.26, J4.BP1, RN16.8 (R1.2), U15.4 (QE), U16.3 (D4)
/BP2: J3.25, J4.BP2, RN16.7 (R2.2), U15.5 (QF), U16.4 (D5)
/BR1: J3.28, J4.BR1, RN16.6 (R3.2), U15.6 (QG), U16.5 (D6)
/BR2: J3.27, J4.BR2, RN16.5 (R4.2), U15.7 (QH), U16.6 (D7)
/BS1: J3.30, J4.BS1, RN17.8 (R1.2), U17.15 (QA), U18.11 (D0)
/BS2: J3.29, J4.BS2, RN17.7 (R2.2), U17.1 (QB), U18.12 (D1)
/BT1: J3.32, JP13.2 (B), RN17.6 (R3.2), U17.2 (QC), U18.13 (D2)
/BT2: J3.31, J4.BT2, RN17.5 (R4.2), U17.3 (QD), U18.14 (D3)
/BU1: J3.34, J4.BU1, RN18.8 (R1.2), U17.4 (QE), U18.3 (D4)
/BU2: J3.33, J4.BU2, RN18.7 (R2.2), U17.5 (QF), U18.4 (D5)
/BV1: J3.36, J4.BV1, RN18.6 (R3.2), U17.6 (QG), U18.5 (D6)
/BV2: J3.35, J4.BV2, RN18.5 (R4.2), U17.7 (QH), U18.6 (D7)
/DRIVER_IN: JP1.3 (B), JP3.1 (A), U1.14 (SER)
/DRIVER_OUT: JP1.1 (A), JP3.3 (B), U17.9 (QH')
/READER_IN: JP2.1 (A), JP4.3 (B), JP5.2 (B), U2.10 (DS)
/READER_OUT: JP2.3 (B), JP4.1 (A), U18.9 (Q7)
DRIVER_OEn: J1.6, JP9.2 (B), U1.13 (~OE), U3.13 (~OE), U5.13 (~OE), U7.13 (~OE), U9.13 (~OE), U11.13 (~OE), U13.13 (~OE), U15.13 (~OE), U17.13 (~OE)
DRIVER_OUTPUT_CLK: J1.17, JP8.2 (B), U1.12 (RCLK), U3.12 (RCLK), U5.12 (RCLK), U7.12 (RCLK), U9.12 (RCLK), U11.12 (RCLK), U13.12 (RCLK), U15.12 (RCLK), U17.12 (RCLK)
DRIVER_SHIFT_CLK: J1.4, JP7.2 (B), U1.11 (SRCLK), U3.11 (SRCLK), U5.11 (SRCLK), U7.11 (SRCLK), U9.11 (SRCLK), U11.11 (SRCLK), U13.11 (SRCLK), U15.11 (SRCLK), U17.11 (SRCLK)
DRIVER_SHIFT_CLRn: J1.7, JP6.2 (B), U1.10 (~SRCLR), U3.10 (~SRCLR), U5.10 (~SRCLR), U7.10 (~SRCLR), U9.10 (~SRCLR), U11.10 (~SRCLR), U13.10 (~SRCLR), U15.10 (~SRCLR), U17.10 (~SRCLR)
GND: C1.2, C2.2, C3.2, C4.2, C5.2, C6.2, C7.2, C8.2, C9.2, C10.2, C11.2, C12.2, C13.2, C14.2, C15.2, C16.2, C17.2, C18.2, C19.2, C20.2, C21.2, C22.2, C23.2, C24.2, C25.2, C26.2, C27.2, J1.3, J1.5, J1.9, J1.11, J1.16, J1.18, J2.37, J2.38, J3.37, J3.38, R1.1, R3.2, R5.2, R7.2, R9.2, R11.2, R13.2, U1.8 (GND), U2.8 (GND), U2.15 (~CE), U3.8 (GND), U4.8 (GND), U4.15 (~CE), U5.8 (GND), U6.8 (GND), U6.15 (~CE), U7.8 (GND), U8.8 (GND), U8.15 (~CE), U9.8 (GND), U10.8 (GND), U10.15 (~CE), U11.8 (GND), U12.8 (GND), U12.15 (~CE), U13.8 (GND), U14.8 (GND), U14.15 (~CE), U15.8 (GND), U16.8 (GND), U16.15 (~CE), U17.8 (GND), U18.8 (GND), U18.15 (~CE)
unnamed: J1.1, JP4.2 (C)
unnamed: J1.2, JP3.2 (C)
unnamed: J1.19, JP1.2 (C)
unnamed: J1.20, JP2.2 (C)
unnamed: J4.AA2, JP14.1 (A)
unnamed: J4.AB2, JP15.1 (A)
unnamed: J4.AC2, JP16.1 (A)
unnamed: J4.AT1, JP12.1 (A)
unnamed: J4.BA2, JP17.1 (A)
unnamed: J4.BB2, JP18.1 (A)
unnamed: J4.BC2, JP19.1 (A)
unnamed: J4.BT1, JP13.1 (A)
unnamed: JP5.1 (A), R1.2
unnamed: JP6.1 (A), R2.2, R3.1
unnamed: JP7.1 (A), R4.2, R5.1
unnamed: JP8.1 (A), R6.2, R7.1
unnamed: JP9.1 (A), R8.2, R9.1
unnamed: JP10.1 (A), R10.2, R11.1
unnamed: JP11.1 (A), R12.2, R13.1
READER_CLK: J1.10, JP11.2 (B), U2.2 (CP), U4.2 (CP), U6.2 (CP), U8.2 (CP), U10.2 (CP), U12.2 (CP), U14.2 (CP), U16.2 (CP), U18.2 (CP)
READER_LOADn: J1.8, JP10.2 (B), U2.1 (~PL), U4.1 (~PL), U6.1 (~PL), U8.1 (~PL), U10.1 (~PL), U12.1 (~PL), U14.1 (~PL), U16.1 (~PL), U18.1 (~PL)

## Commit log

2024-08-05 Added files sent for prototyping and updated README
2024-08-05 Actually added files
